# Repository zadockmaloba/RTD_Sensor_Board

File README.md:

# Zadock Maloba - Instrumentation & Control Engineer Design Challenge

## The System

A lab-scale thermal test bench. Sixteen RTDs are distributed along a heated circuit; a
coolant admission valve opens and closes to hold the circuit within band. The bench runs
unattended for days at a time, and the resulting temperature record is the deliverable that
engineers downstream actually care about.

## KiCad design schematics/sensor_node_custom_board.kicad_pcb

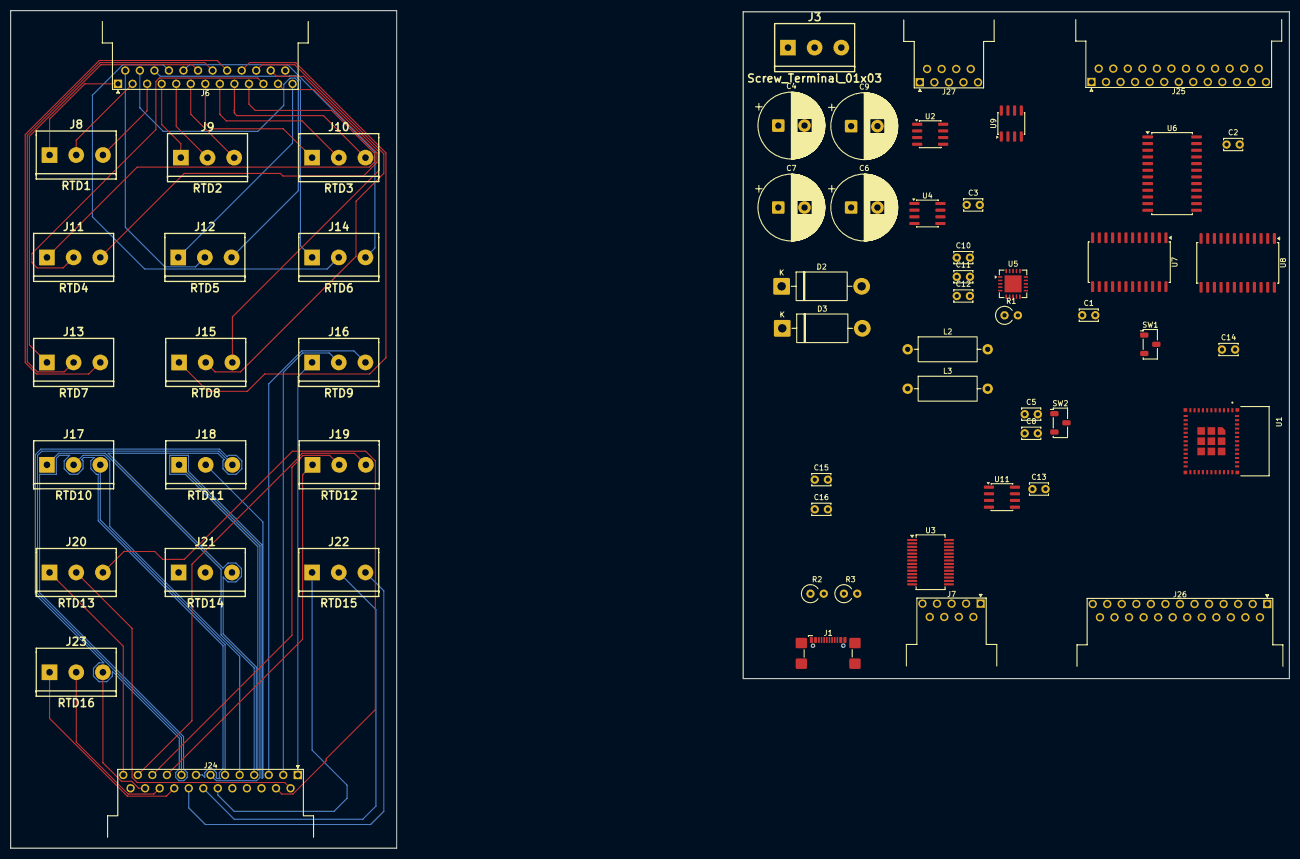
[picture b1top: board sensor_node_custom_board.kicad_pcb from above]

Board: 2 copper layers, 243.5 x 159.5 mm, 59 parts (0 on the bottom side), 132 nets.

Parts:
C1, C2, C13, C14, C15, C16: 0.1uF; C_Disc_D3.4mm_W2.1mm_P2.50mm
C3, C10, C11: 10uF; C_Disc_D3.4mm_W2.1mm_P2.50mm
C4, C7: 470uF/50V; CP_Radial_D12.5mm_P5.00mm
C5, C8: 105; C_Disc_D3.4mm_W2.1mm_P2.50mm
C6: 330uF/35V; CP_Radial_D12.5mm_P5.00mm
C9: 180uF/35V; CP_Radial_D12.5mm_P5.00mm
C12: 10nF; C_Disc_D3.4mm_W2.1mm_P2.50mm
D2, D3: 1N5822; D_DO-201AD_P15.24mm_Horizontal
J1: USB_C_Receptacle_USB2.0_16P; USB_C_Receptacle_GCT_USB4110
J3: Screw_Terminal_01x03; mors_3p
J6: RTD_A (Breakout); DSUB-25_Socket_Horizontal_P2.77x2.54mm_EdgePinOffset9.40mm
J7: MODBUS RTU; DSUB-9_Socket_Horizontal_P2.77x2.54mm_EdgePinOffset9.40mm
J8: RTD1; mors_3p
J9: RTD2; mors_3p
J10: RTD3; mors_3p
J11: RTD4; mors_3p
J12: RTD5; mors_3p
J13: RTD7; mors_3p
J14: RTD6; mors_3p
J15: RTD8; mors_3p
J16: RTD9; mors_3p
J17: RTD10; mors_3p
J18: RTD11; mors_3p
J19: RTD12; mors_3p
J20: RTD13; mors_3p
J21: RTD14; mors_3p
J22: RTD15; mors_3p
J23: RTD16; mors_3p
J24: RTD_B (Breakout); DSUB-25_Socket_Horizontal_P2.77x2.54mm_EdgePinOffset9.40mm
J25: RTD_A; DSUB-25_Socket_Horizontal_P2.77x2.54mm_EdgePinOffset9.40mm
J26: RTD_B; DSUB-25_Socket_Horizontal_P2.77x2.54mm_EdgePinOffset9.40mm
J27: CAN; DSUB-9_Socket_Horizontal_P2.77x2.54mm_EdgePinOffset9.40mm
L2, L3: 68uH; L_Axial_L11.0mm_D4.5mm_P15.24mm_Horizontal_Fastron_MECC
R1: 4k; R_Axial_DIN0309_L9.0mm_D3.2mm_P2.54mm_Vertical
R2, R3: 5.1k; R_Axial_DIN0309_L9.0mm_D3.2mm_P2.54mm_Vertical
SW1: SW_ESP_ EN; Nidec_Copal_CAS-120A
SW2: SW_Nidec_CAS-120A1; Nidec_Copal_CAS-120A
U1: ESP32-PICO-MINI-02; MODULE_ESP32-PICO-MINI-02
U2: XL1509-5.0; SOIC-8_3.9x4.9mm_P1.27mm
U3: FT232RL; SSOP-28_5.3x10.2mm_P0.65mm
U4: XL1509-3.3; SOIC-8_3.9x4.9mm_P1.27mm
U5: MAX31865xTP; TQFN-20-1EP_5x5mm_P0.65mm_EP3.25x3.25mm
U6, U7, U8: CD74HC4067M; SOIC-24W_7.5x15.4mm_P1.27mm
U9: SN65HVD255D; SOIC-8_3.9x4.9mm_P1.27mm
U11: ISL3175E; SOIC-8_3.9x4.9mm_P1.27mm

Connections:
/Control Board/CAN Bus Controller/CANH: J27.7, U9.7 (CANH)
/Control Board/CAN Bus Controller/CANL: J27.2, U9.6 (CANL)
/Control Board/ESP_RXD0: U1.30 (RXD0), U3.5 (RXD), U11.1 (RO)
/Control Board/ESP_TXD0: U1.31 (TXD0), U3.1 (TXD), U11.4 (DI)
/Control Board/HSPI_CLK: U1.18 (IO14), U5.12 (SCLK)
/Control Board/HSPI_CS: U1.21 (IO15), U5.13 (~CS)
/Control Board/HSPI_MISO: U1.19 (IO12), U5.14 (SDO)
/Control Board/HSPI_MOSI: U1.20 (IO13), U5.11 (SDI)
/Control Board/ISL_DE: U1.16 (IO26), U11.3 (DE)
/Control Board/MCU/ESP_EN: SW1.2 (B), U1.8 (EN)
/Control Board/MUX_CTL0: U1.33 (IO19), U6.10 (S0), U7.10 (S0), U8.10 (S0)
/Control Board/MUX_CTL1: U1.26 (IO20), U6.11 (S1), U7.11 (S1), U8.11 (S1)
/Control Board/MUX_CTL2: U1.35 (IO21), U6.14 (S2), U7.14 (S2), U8.14 (S2)
/Control Board/MUX_CTL3: U1.34 (IO22), U6.13 (S3), U7.13 (S3), U8.13 (S3)
/Control Board/Power Supply/COM_GND: C1.2, C2.2, C3.2, C4.2, C5.2, C6.2, C7.2, C8.2, C9.2, C10.2, C11.2, C13.1, C14.2, C15.2, C16.2, D2.2 (A), D3.2 (A), J1.A1 (GND), J1.A12 (GND), J1.B1 (GND), J1.B12 (GND), J1.SH (SHIELD), J3.2, J27.3, R2.2, R3.2, SW1.1 (C), SW2.2 (B), U1.1 (GND), U1.2 (GND__1), U1.11 (GND__2), U1.14 (GND__3), U1.36 (GND__4), U1.37 (GND__5), U1.38 (GND__6), U1.39 (GND__7), U1.40 (GND__8), U1.41 (GND__9), U1.42 (GND__10), U1.43 (GND__11), U1.44 (GND__12), U1.45 (GND__13), U1.46 (GND__14), U1.47 (GND__15), U1.48 (GND__16), U1.49 (GND__17), U1.50 (GND__18), U1.51 (GND__19), U1.52 (GND__20), U1.53 (GND__21), U1.54 (GND__22), U1.55 (GND__23), U1.56 (GND__24), U1.57 (GND__25), U1.58 (GND__26), U1.59 (GND__27), U1.60 (GND__28), U1.61 (GND__29), U2.5 (GND), U2.6 (GND), U2.7 (GND), U2.8 (GND), U3.7 (GND), U3.18 (GND), U3.21 (GND), U3.25 (AGND), U4.5 (GND), U4.6 (GND), U4.7 (GND), U4.8 (GND), U5.10 (GND), U5.15 (DGND), U5.16 (GND), U5.21 (GND), U6.12 (GND), U7.12 (GND), U8.12 (GND), U9.2 (GND), U11.5 (GND)
/Control Board/Power Supply/POWER_ON: SW2.1 (C), U2.4 (~EN), U4.4 (~EN)
/Control Board/Power Supply/VBUS_3V3: C1.1, C2.1, C3.1, C6.1, C9.1, C10.1, C11.1, C13.2, C14.1, C15.1, C16.1, J27.9, L2.2, L3.2, SW1.3 (A), U1.3 (3V3), U2.3 (FB), U3.4 (VCCIO), U3.20 (VCC), U4.3 (FB), U5.19 (DVDD), U5.20 (VDD), U6.24 (VCC), U7.24 (VCC), U8.24 (VCC), U9.3 (VCC), U11.8 (VCC)
/Control Board/Power Supply/VBUS_24: C4.1, C5.1, C7.1, C8.1, J3.1, U2.1 (VIN), U4.1 (VIN)
/Control Board/Programmer & Debugger/USBD+: J1.A6 (D+), J1.B6 (D+), U3.15 (USBD+)
/Control Board/Programmer & Debugger/USBD-: J1.A7 (D-), J1.B7 (D-), U3.16 (USBD-)
/Control Board/RS-485 Controller/MODBUS_TA: J7.8, U11.6 (A)
/Control Board/RS-485 Controller/MODBUS_TB: J7.3, U11.7 (B)
/Control Board/Sensor IO/F+0: J25.1, U7.9 (I0)
/Control Board/Sensor IO/F+1: J25.4, U7.8 (I1)
/Control Board/Sensor IO/F+2: J25.7, U7.7 (I2)
/Control Board/Sensor IO/F+3: J25.10, U7.6 (I3)
/Control Board/Sensor IO/F+4: J25.13, U7.5 (I4)
/Control Board/Sensor IO/F+5: J25.16, U7.4 (I5)
/Control Board/Sensor IO/F+6: J25.19, U7.3 (I6)
/Control Board/Sensor IO/F+7: J25.22, U7.2 (I7)
/Control Board/Sensor IO/F+8: J26.1, U7.23 (I8)
/Control Board/Sensor IO/F+9: J26.4, U7.22 (I9)
/Control Board/Sensor IO/F+10: J26.7, U7.21 (I10)
/Control Board/Sensor IO/F+11: J26.10, U7.20 (I11)
/Control Board/Sensor IO/F+12: J26.13, U7.19 (I12)
/Control Board/Sensor IO/F+13: J26.16, U7.18 (I13)
/Control Board/Sensor IO/F+14: J26.19, U7.17 (I14)
/Control Board/Sensor IO/F+15: J26.22, U7.16 (I15)
/Control Board/Sensor IO/MAX_FORCE+: U5.5 (FORCE+), U5.6 (FORCE2), U7.1 (COM)
/Control Board/Sensor IO/MAX_RTDIN+: C12.1, U5.7 (RTDIN+), U6.1 (COM)
/Control Board/Sensor IO/MAX_RTDIN-: C12.2, U5.8 (RTDIN-), U5.9 (FORCE-), U8.1 (COM)
/Control Board/Sensor IO/RTDIN+0: J25.2, U6.9 (I0)
/Control Board/Sensor IO/RTDIN+1: J25.5, U6.8 (I1)
/Control Board/Sensor IO/RTDIN+2: J25.8, U6.7 (I2)
/Control Board/Sensor IO/RTDIN+3: J25.11, U6.6 (I3)
/Control Board/Sensor IO/RTDIN+4: J25.14, U6.5 (I4)
/Control Board/Sensor IO/RTDIN+5: J25.17, U6.4 (I5)
/Control Board/Sensor IO/RTDIN+6: J25.20, U6.3 (I6)
/Control Board/Sensor IO/RTDIN+7: J25.23, U6.2 (I7)
/Control Board/Sensor IO/RTDIN+8: J26.2, U6.23 (I8)
/Control Board/Sensor IO/RTDIN+9: J26.5, U6.22 (I9)
/Control Board/Sensor IO/RTDIN+10: J26.8, U6.21 (I10)
/Control Board/Sensor IO/RTDIN+11: J26.11, U6.20 (I11)
/Control Board/Sensor IO/RTDIN+12: J26.14, U6.19 (I12)
/Control Board/Sensor IO/RTDIN+13: J26.17, U6.18 (I13)
/Control Board/Sensor IO/RTDIN+14: J26.20, U6.17 (I14)
/Control Board/Sensor IO/RTDIN+15: J26.23, U6.16 (I15)
/Control Board/Sensor IO/RTDIN-0: J25.3, U8.9 (I0)
/Control Board/Sensor IO/RTDIN-1: J25.6, U8.8 (I1)
/Control Board/Sensor IO/RTDIN-2: J25.9, U8.7 (I2)
/Control Board/Sensor IO/RTDIN-3: J25.12, U8.6 (I3)
/Control Board/Sensor IO/RTDIN-4: J25.15, U8.5 (I4)
/Control Board/Sensor IO/RTDIN-5: J25.18, U8.4 (I5)
/Control Board/Sensor IO/RTDIN-6: J25.21, U8.3 (I6)
/Control Board/Sensor IO/RTDIN-7: J25.24, U8.2 (I7)
/Control Board/Sensor IO/RTDIN-8: J26.3, U8.23 (I8)
/Control Board/Sensor IO/RTDIN-9: J26.6, U8.22 (I9)
/Control Board/Sensor IO/RTDIN-10: J26.9, U8.21 (I10)
/Control Board/Sensor IO/RTDIN-11: J26.12, U8.20 (I11)
/Control Board/Sensor IO/RTDIN-12: J26.15, U8.19 (I12)
/Control Board/Sensor IO/RTDIN-13: J26.18, U8.18 (I13)
/Control Board/Sensor IO/RTDIN-14: J26.21, U8.17 (I14)
/Control Board/Sensor IO/RTDIN-15: J26.24, U8.16 (I15)
/Control Board/TWAI_RX: U1.24 (IO4), U9.4 (RXD)
/Control Board/TWAI_TX: U1.29 (IO5), U9.1 (TXD)
/Control Board/~ISL_RE: U1.17 (IO27), U11.2 (~RE)
/Control Board/~MUX_E: U1.15 (IO25), U6.15 (~E), U7.15 (~E), U8.15 (~E)
/Control Board/~SEN_DRDY: U1.10 (I35), U5.18 (~DRDY)
/IO Breakout Board/RTD_A0: J6.1, J8.1
/IO Breakout Board/RTD_A1: J6.2, J8.2
/IO Breakout Board/RTD_A2: J6.3, J8.3
/IO Breakout Board/RTD_A3: J6.4, J9.1
/IO Breakout Board/RTD_A4: J6.5, J9.2
/IO Breakout Board/RTD_A5: J6.6, J9.3
/IO Breakout Board/RTD_A6: J6.7, J10.1
/IO Breakout Board/RTD_A7: J6.8, J10.2
/IO Breakout Board/RTD_A8: J6.9, J10.3
/IO Breakout Board/RTD_A9: J6.10, J11.1
/IO Breakout Board/RTD_A10: J6.11, J11.2
/IO Breakout Board/RTD_A11: J6.12, J11.3
/IO Breakout Board/RTD_A12: J6.13, J12.1
/IO Breakout Board/RTD_A13: J6.14, J12.2
/IO Breakout Board/RTD_A14: J6.15, J12.3
/IO Breakout Board/RTD_A15: J6.16, J14.1
/IO Breakout Board/RTD_A16: J6.17, J14.2
/IO Breakout Board/RTD_A17: J6.18, J14.3
/IO Breakout Board/RTD_A18: J6.19, J13.1
/IO Breakout Board/RTD_A19: J6.20, J13.2
/IO Breakout Board/RTD_A20: J6.21, J13.3
/IO Breakout Board/RTD_A21: J6.22, J15.1
/IO Breakout Board/RTD_A22: J6.23, J15.2
/IO Breakout Board/RTD_A23: J6.24, J15.3
/IO Breakout Board/RTD_B0: J16.1, J24.1
/IO Breakout Board/RTD_B1: J16.2, J24.2
/IO Breakout Board/RTD_B2: J16.3, J24.3
/IO Breakout Board/RTD_B3: J17.1, J24.4
/IO Breakout Board/RTD_B4: J17.2, J24.5
/IO Breakout Board/RTD_B5: J17.3, J24.6
/IO Breakout Board/RTD_B6: J18.1, J24.7
/IO Breakout Board/RTD_B7: J18.2, J24.8
/IO Breakout Board/RTD_B8: J18.3, J24.9
/IO Breakout Board/RTD_B9: J19.1, J24.10
/IO Breakout Board/RTD_B10: J19.2, J24.11
/IO Breakout Board/RTD_B11: J19.3, J24.12
/IO Breakout Board/RTD_B12: J20.1, J24.13
/IO Breakout Board/RTD_B13: J20.2, J24.14
/IO Breakout Board/RTD_B14: J20.3, J24.15
/IO Breakout Board/RTD_B15: J21.1, J24.16
/IO Breakout Board/RTD_B16: J21.2, J24.17
/IO Breakout Board/RTD_B17: J21.3, J24.18
/IO Breakout Board/RTD_B18: J22.1, J24.19
/IO Breakout Board/RTD_B19: J22.2, J24.20
/IO Breakout Board/RTD_B20: J22.3, J24.21
/IO Breakout Board/RTD_B21: J23.1, J24.22
/IO Breakout Board/RTD_B22: J23.2, J24.23
/IO Breakout Board/RTD_B23: J23.3, J24.24
unnamed: D2.1 (K), L2.1, U4.2 (OUT)
unnamed: D3.1 (K), L3.1, U2.2 (OUT)
unnamed: J1.A5 (CC1), R2.1
unnamed: J1.B5 (CC2), R3.1
unnamed: R1.1, U5.1 (BIAS), U5.2 (REFIN+)
unnamed: R1.2, U5.3 (REFIN-), U5.4 (ISENSOR)
